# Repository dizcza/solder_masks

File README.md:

# PCB DXF solder masks

To be lasercut for PCB assembly.

PCB file has a collection of desired footprints (Kicad v8).

## Example

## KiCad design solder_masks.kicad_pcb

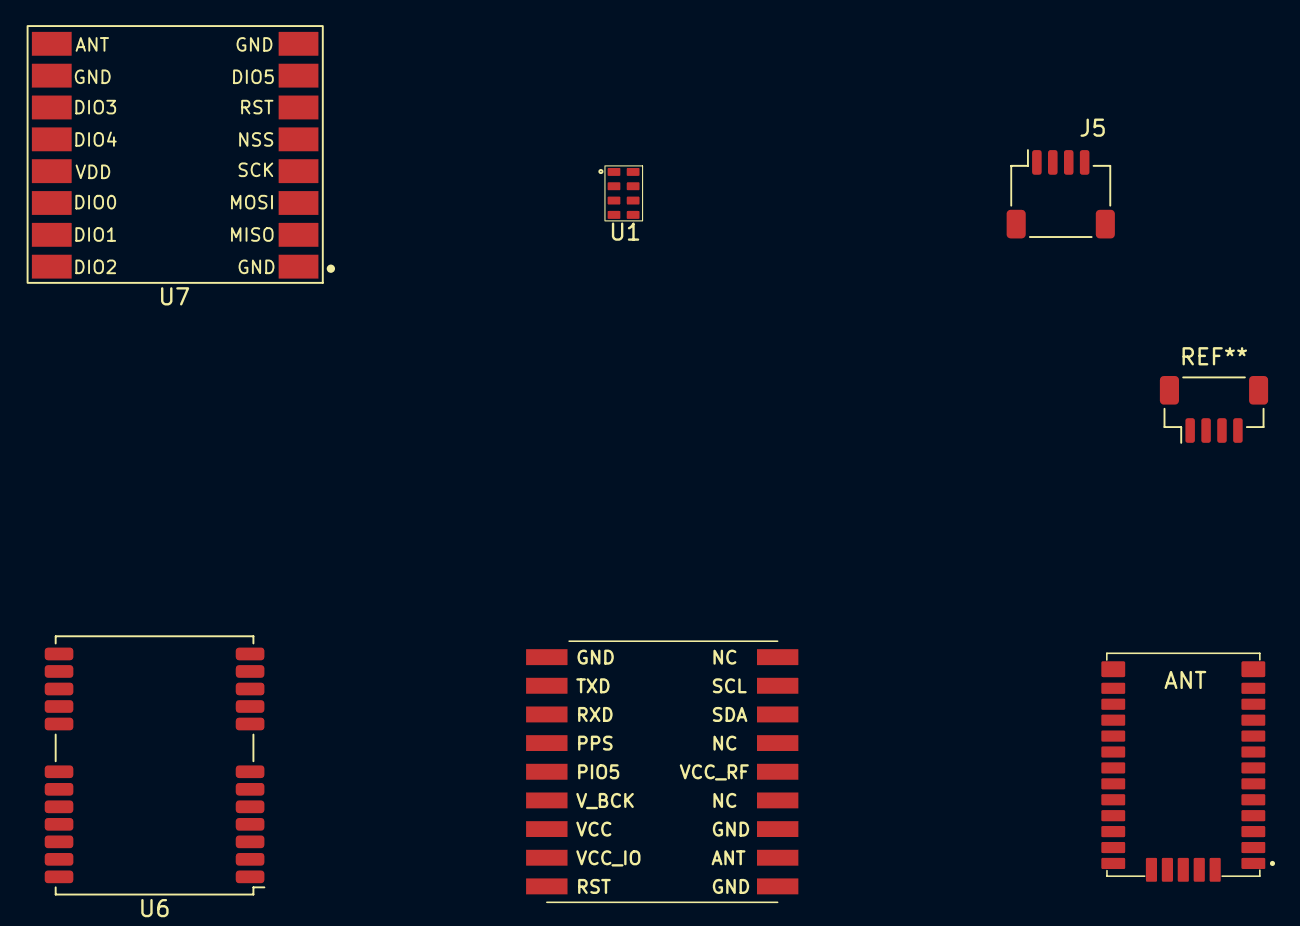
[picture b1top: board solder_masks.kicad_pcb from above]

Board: 2 copper layers, 6 parts (0 on the bottom side), 2 nets, no tracks yet.

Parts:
J5: SH_Conn_01x04; JST_SH_SM04B-SRSS-TB_1x04-1MP_P1.00mm_Horizontal
U1: CAM-M8C
U1#2: RV-3032
U4: G-NiceRF-GPS
U6: NEO-M8P; ublox_NEO
U7: SX1276

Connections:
+3V3: U6.22 (V_BCKP), U6.23 (VCC), U7.11 (VDD)
GND: U6.7 (VDD_USB), U6.10 (GND), U6.12 (GND), U6.13 (GND), U6.24 (GND), U7.1 (GND)

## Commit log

2024-03-01 gps, lora, rv-3032 solder masks
2024-03-01 A5 layout
2024-03-20 SH1.0 4P connector
2024-04-19 sh1.0 vertical
